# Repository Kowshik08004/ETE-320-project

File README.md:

# 🎓 RFID-Based Attendance Management System

A comprehensive web-based attendance management system using RFID technology for automated student attendance tracking. Built for educational institutions to streamline attendance recording, monitoring, and reporting.

## ✨ Features

### 🔐 Admin Features
- **User Management**: Add, edit, and delete student records
- **Course Management**: Create and manage courses, sections, and batches
- **Device Management**: Configure and monitor RFID readers
- **Room & Batch Assignment**: Link rooms with devices and student batches
- **Session Management**: Create manual or automatic class sessions
- **Attendance Reports**: 
  - View real-time attendance
  - Generate attendance summaries
  - Export to Excel, CSV, and PDF formats
- **Weekly Routines**: Auto-generate class schedules
- **User Activity Logs**: Track system usage and changes

### 📊 Attendance Features
- Automatic attendance recording via RFID
- Real-time attendance monitoring
- Session-based attendance tracking
- Attendance percentage calculation
- Course-wise attendance reports
- Auto-close expired sessions

### 🔧 Technical Features
- Responsive web interface
- Secure authentication system
- Database-driven architecture
- AJAX-powered real-time updates
- Export functionality (Excel, CSV, PDF)
- Automated session cleanup

## 🏗️ System Architecture

## 📋 Prerequisites

Before you begin, ensure you have the following installed:

- **Web Server**: Apache (XAMPP, WAMP, or LAMP)
- **PHP**: Version 7.4 or higher
- **MySQL**: Version 5.7 or higher
- **Arduino IDE**: For programming the RFID reader (if using hardware)
- **RFID Reader**: RC522 or compatible
- **Modern Web Browser**: Chrome, Firefox, Edge, or Safari

## 🚀 Installation

### Step 1: Clone the Repository

```bash
git clone https://github.com/Kowshik08004/ETE-320-project.git
cd ETE-320-project
```

### Step 2: Setup Database

1. Start your MySQL server (via XAMPP/WAMP)
2. Open phpMyAdmin (http://localhost/phpmyadmin)
3. Create a new database named `rfidattendance`
4. Import the database schema:
   - Click on the `rfidattendance` database
   - Go to the **Import** tab
   - Select `rfidattendance.sql` file
   - Click **Go**

### Step 3: Configure Database Connection

1. Open `connectDB.php` in a text editor
2. Update the database credentials:

```php
$servername = "localhost";
$username = "root";        // Your MySQL username
$password = "";            // Your MySQL password
$dbname = "rfidattendance";
```

### Step 4: Deploy Application

1. Copy the project folder to your web server's root directory:
   - **XAMPP**: `C:\xampp\htdocs\`
   - **WAMP**: `C:\wamp64\www\`
   - **LAMP**: `/var/www/html/`

2. Ensure proper file permissions (Linux/Mac):
```bash
sudo chmod -R 755 /var/www/html/ETE-320-project
```

### Step 5: Access the Application

1. Open your web browser
2. Navigate to: `http://localhost/ETE-320-project`
3. Login with default credentials:
   - **Email**: `admin@gmail.com`
   - **Password**: `123` (or check the SQL dump for the hashed password)

## 🔌 Hardware Setup

### Components Needed
- ESP32-wroom-32
- MFRC522 RFID Reader Module
- RFID Cards
- DS3231 RTC
- 16x2 LCD display
- Buzzer
- 100k Trimmerpot

### Wiring Diagram

### Upload Arduino Code

1. Open Arduino IDE
2. Install required library: **SPI, Wire, MFRC522, RTClib, LiquidCrystal, WiFi, HTTPClient** (Tools → Manage Libraries → Search "MFRC522")
3. Open `RFID/RFID.ino`
4. Select your board and port
5. Upload the sketch

## 📖 Usage Guide

### For Administrators

1. **Add Students**
   - Navigate to "Manage Users"
   - Scan an unregistered card. It will appear in the list.
   - select it (Click on the card). RFID card will be automatically filled. Enter student details & click Register Student.

2. **Create Course Sessions**
   - Go to "Course Sessions"
   - Create session (manual)
   - Fill all the necessary info. 
   - Click create session

3. **View Attendance**
   - Navigate to "Attendance View"
   - Select course and date range
   - View or export reports

4. **Setup Weekly Routines**
   - Go to "Weekly Routines"
   - Configure class schedules
   - Enable auto-generation

### For Students

- Simply tap your RFID card on the reader when entering class
- Attendance is automatically recorded
- No manual login required

## 📁 Project Structure

```
ETE-320-project/
│
├── RFID/                          # Arduino code for RFID reader
│   ├── RFID.ino
│   └── rfid_attendance/           # KiCad PCB design files
│
├── js/                            # JavaScript files
│   ├── jquery-2.2.3.min.js
│   ├── bootstrap.js
│   └── *.js                       # Custom scripts
│
├── icons/                         # UI icons
│
├── css/                           # Stylesheets
│
├── *.php                          # PHP application files
│   ├── index.php                  # Main dashboard
│   ├── login.php                  # Authentication
│   ├── connectDB.php              # Database connection
│   ├── ManageUsers.php            # User management
│   ├── ManageCourses.php          # Course management
│   ├── attendance_view.php        # Attendance reports
│   └── ...                        # Other modules
│
├── rfidattendance.sql             # Database schema
├── composer.json                   # PHP dependencies
└── README.md                      # This file
```

## 🔒 Security Features

- ✅ Session-based authentication
- ✅ Admin guard middleware
- ✅ Password hashing (bcrypt)
- ✅ SQL injection prevention
- ✅ XSS protection
- ✅ CSRF token validation (recommended to implement)

## 🐛 Troubleshooting

### Common Issues

**Database Connection Failed**
- Check MySQL service is running
- Verify credentials in `connectDB.php`
- Ensure database `rfidattendance` exists

**RFID Not Reading**
- Check Arduino connections
- Verify COM port in Arduino IDE
- Test RFID cards are not damaged
- Ensure MFRC522 library is installed

**Attendance Not Recording**
- Verify student RFID is registered in database
- Check active session exists for the course
- Ensure device is linked to correct room

**Export Not Working**
- Check PHP extensions: `php_zip`, `php_excel`
- Verify write permissions on export directory
- Check PHP memory limit in `php.ini`

## 🤝 Contributing

Contributions are welcome! Please follow these steps:

1. Fork the repository
2. Create a feature branch (`git checkout -b feature/AmazingFeature`)
3. Commit your changes (`git commit -m 'Add some AmazingFeature'`)
4. Push to the branch (`git push origin feature/AmazingFeature`)
5. Open a Pull Request

## 📝 Development Roadmap

- [ ] Add SMS/Email notifications for absent students
- [ ] Implement facial recognition as alternative to RFID
- [ ] Create mobile app for students
- [ ] Add biometric authentication
- [ ] Real-time analytics dashboard
- [ ] Multi-language support
- [ ] RESTful API for third-party integrations

## 📄 License

This project is licensed under the MIT License - see the [LICENSE](LICENSE) file for details.

## 👥 Authors

- **Kowshik Chowdhury** - [GitHub](https://github.com/Kowshik08004)

## 🙏 Acknowledgments

- CUET ETE-320 Course Project
- MFRC522 Library developers
- Bootstrap framework
- All contributors and testers

## 📧 Contact

For questions or support, please contact:
- **Email**: u2108004@student.cuet.ac.bd
- **Project Link**: [https://github.com/Kowshik08004/ETE-320-project](https://github.com/Kowshik08004/ETE-320-project)

---

<div align="center">

⭐ Star this repo if you find it helpful!

</div>

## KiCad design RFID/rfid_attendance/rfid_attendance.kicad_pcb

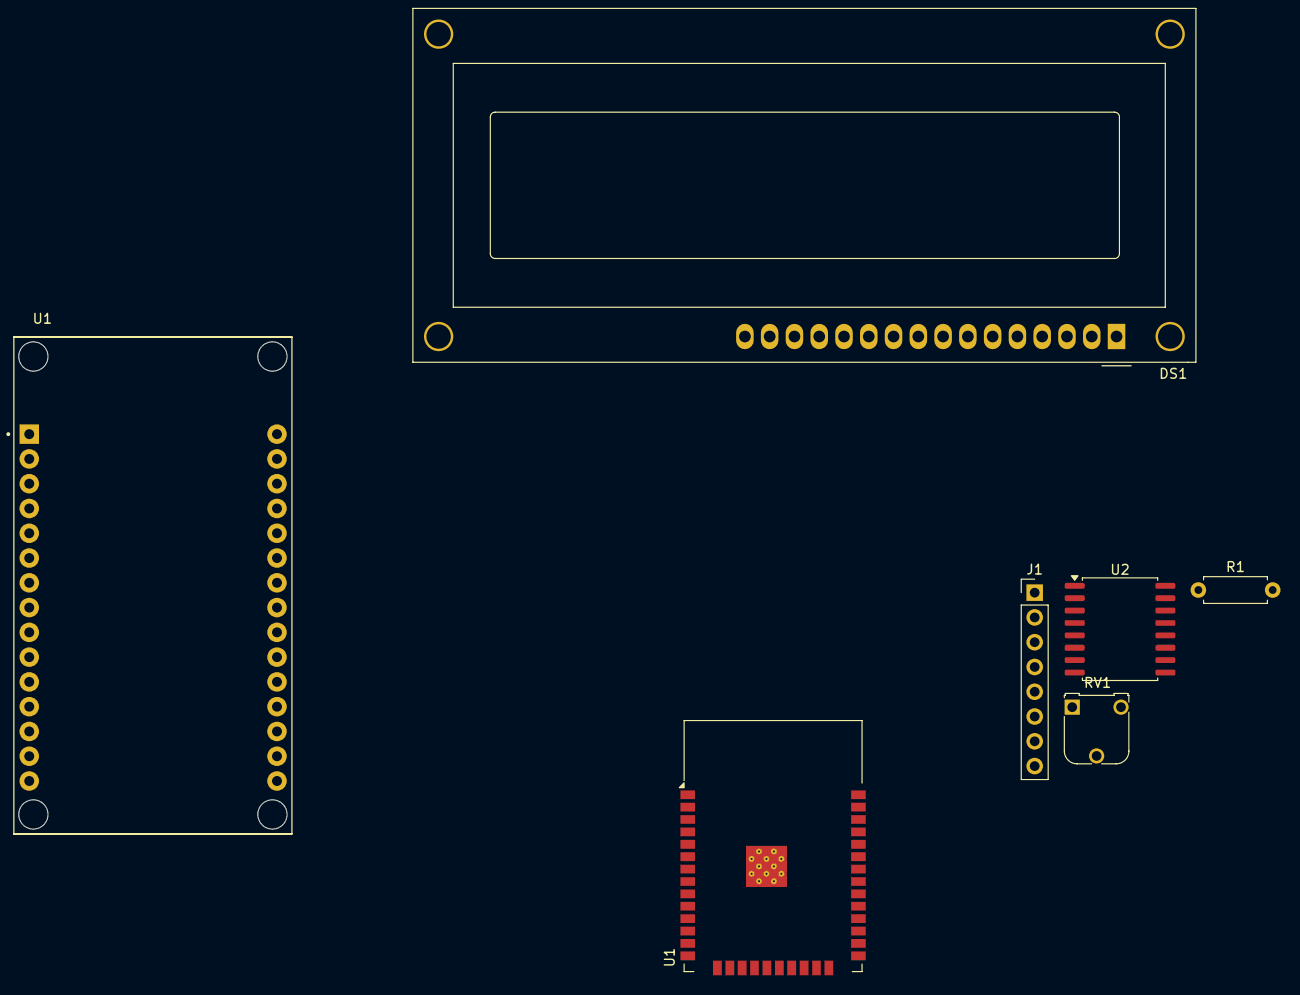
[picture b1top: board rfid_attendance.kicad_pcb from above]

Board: 2 copper layers, 7 parts (0 on the bottom side), 3 nets, no tracks yet.

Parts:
DS1: LCD; WC1602A
J1: RC522; PinHeader_1x08_P2.54mm_Vertical
R1: 220R; R_Axial_DIN0207_L6.3mm_D2.5mm_P7.62mm_Horizontal
RV1: 100k; Potentiometer_Runtron_RM-065_Vertical
U1: ESP32-WROOM-32
U1#2: ESP32-DEVKIT-V1; MODULE_ESP32_DEVKIT_V1
U2: RTC; SOIC-16W_7.5x10.3mm_P1.27mm

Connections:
GND: U1#2.2 (GND), U1#2.29 (GND)
unnamed: U1.1 (GND), U1.15 (GND), U1.38 (GND), U1.39 (GND)
unnamed: U2.5 (GND), U2.6 (GND), U2.7 (GND), U2.8 (GND), U2.9 (GND), U2.10 (GND), U2.11 (GND), U2.12 (GND), U2.13 (GND)

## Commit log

2026-01-21 Add project title to README.md
2026-01-30 Add initial project files and documentation
    Added .gitignore, LICENSE, contributing guidelines, quickstart, and documentation files. Updated README.md with detailed project overview, setup instructions, and features. Included example database 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
2026-01-30 Update repository URLs and contact info in docs
    Replaced placeholder GitHub URLs with the actual repository link in GITHUB_CHECKLIST.md, QUICKSTART.md, and README.md. Updated default password in QUICKSTART.md and revised contact email and project 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
2026-01-30 Update README and add system diagrams
    Added system architecture and wiring diagram images to the screenshots directory and referenced them in the README. Updated admin password, author information, and contact email in the documentation.
2026-01-30 Update image references in README
    Replaced outdated system architecture and wiring diagram images with updated file paths in the README. Removed the ASCII diagram for system architecture.
2026-01-30 Update hardware setup and instructions in README
    Revised the hardware components list to use ESP32 and additional modules, updated the wiring diagram section, and clarified the steps for library installation and user management. These changes refle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
2026-01-30 Add screenshots for various application features
    Added multiple PNG screenshots to the screenshots directory, covering features such as course addition, admin panel, attendance summary, device management, login, and more. These images can be used f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

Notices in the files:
README.md:
License: MIT
